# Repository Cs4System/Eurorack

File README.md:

# Eurorack

- All files are published under CC BY-NC-SA 4.0 if not marked differently

- DO NOT USE COMMERCIALLY!

- Build for yourself or for a friend, but do not sell builds, PCBs, pannels or any parts of the designes in this repository! 

- Feel free to modify, copy and use all files provided here. 
If you want to publish derivative work, please do so under same license as original

- Any feedback and collaboration is very welcome!

- Please feel free to [open an issue on the issues tab](https://github.com/Cs4System/Eurorack/issues)

**Have you built a module and would like to say thank you?** https://paypal.me/LorenzNeumann

## [Blattwerk - Betula](https://github.com/Cs4System/Eurorack/tree/main/Betula)

- 8 channels In/Out ADAT Interface
- Outputs are DC coupled
- Inputs can be switched with jumpers between AC and DC coupling (In 2 groups: channel 1-4 and channel 5-8)
- Low noise: -110dB
- Low THD: >0.01% @ 1kHz, -6dB(+-5Vpp)
- 22kOhm input-impedance, 1kOhm output-impedance
- 8HP
- All channels with bicolored indicator LED
- ADAT sync indicator LED
- No μController, no programming required, hardware only
- CC BY-NC-SA 4.0 DO NOT USE COMMERCIALY!
- small and dense SMD build (0603,TSSOP)
- 180mA @ +12V and 100mA @ -12V
(Without connected ADTA-signal:
14mA @ +12V and 0mA @ -12V)

## [Blattwerk - Salix](https://github.com/Cs4System/Eurorack/tree/main/Salix)

- VCF based on the Moog Transistor Ladder Filter
- Compensation for loss of bass in high resonance settings via potentiometer
- 6,12,18,24 dB/Oct selectable via potentiometer or CV!
- 2 Inputs with attenuator for audio and CV
- Seperate V/Oct input.
- Input-Drive indicator LED
- 8HP
- small and dense SMD build (0603, SOIC, SOT-363!) Not a beginner build, please be sure to have some SMD-soldering practice!
- 45mA @ +12V and 25mA @ -12V
- quick demo: https://youtu.be/XMdGtwIK5IQ

## [Transistor Ladder VCF](https://github.com/Cs4System/Eurorack/tree/main/Transistor_Ladder_VCF)

- Deprecated version of [Salix VCF](https://github.com/Cs4System/Eurorack/tree/main/Salix)
- VCF based on the Moog Transistor Ladder Filter
- Compensation for loss of bass in high resonance settings via potentiometer
- 6,12,18,24 dB/Oct selectable via potentiometer or CV!
- 2 Inputs with attenuator for audio and CV
- Seperate V/Oct input.
- Input-Drive indicator LED
- 8HP
- CC BY-NC-SA 4.0
- small and dense SMD build (0603, SOIC, SOT-363!)
- 45mA @ +12V and 25mA @ -12V
- PCB and Panel  is available at [synthCube](https://synthcube.com/cart/lorenz-neumann-diy-transistor-ladder-filter)
- Quick demo: https://youtu.be/XMdGtwIK5IQ

## [Dual Ears](https://github.com/Cs4System/Eurorack/tree/main/Dual%20Ears)
- BETA!
- Modification of Mutable Instruments Ears
- 2 seperat channels of original design, no internal contact microphone
- no jumpers, fixed values for fast Envelope Follower and Gate-Threshold of 1V 
- 4HP
- CC-BY-SA 3.0, Orginal schematics by Emilie Gillet
- small and dense SMD build (0603, TSSOP)

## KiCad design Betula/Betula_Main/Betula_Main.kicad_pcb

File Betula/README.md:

# Blattwerk - Betula

- 8 channels In/Out ADAT Interface
- Outputs are DC coupled
- Inputs can be switched with jumpers between AC and DC coupling (In 2 groups: channel 1-4 and channel 5-8)
- Low noise: -110dB
- Low THD: >0.01% @ 1kHz, -6dB(+-5Vpp)
- 22kOhm input-impedance, 1kOhm output-impedance
- 8HP
- All channels with bicolored indicator LED
- ADAT sync indicator LED
- No μController, no programming required, hardware only
- CC BY-NC-SA 4.0 DO NOT USE COMMERCIALY!
- small and dense SMD build (0603,TSSOP)
- 180mA @ +12V and 100mA @ -12V
(Without connected ADTA-signal:
14mA @ +12V and 0mA @ -12V)

For comments and feedback, please visit [Modwiggler](https://www.modwiggler.com/forum/viewtopic.php?t=283803&sid=8c5b24ebdf0f756f3375e19afba1d032)

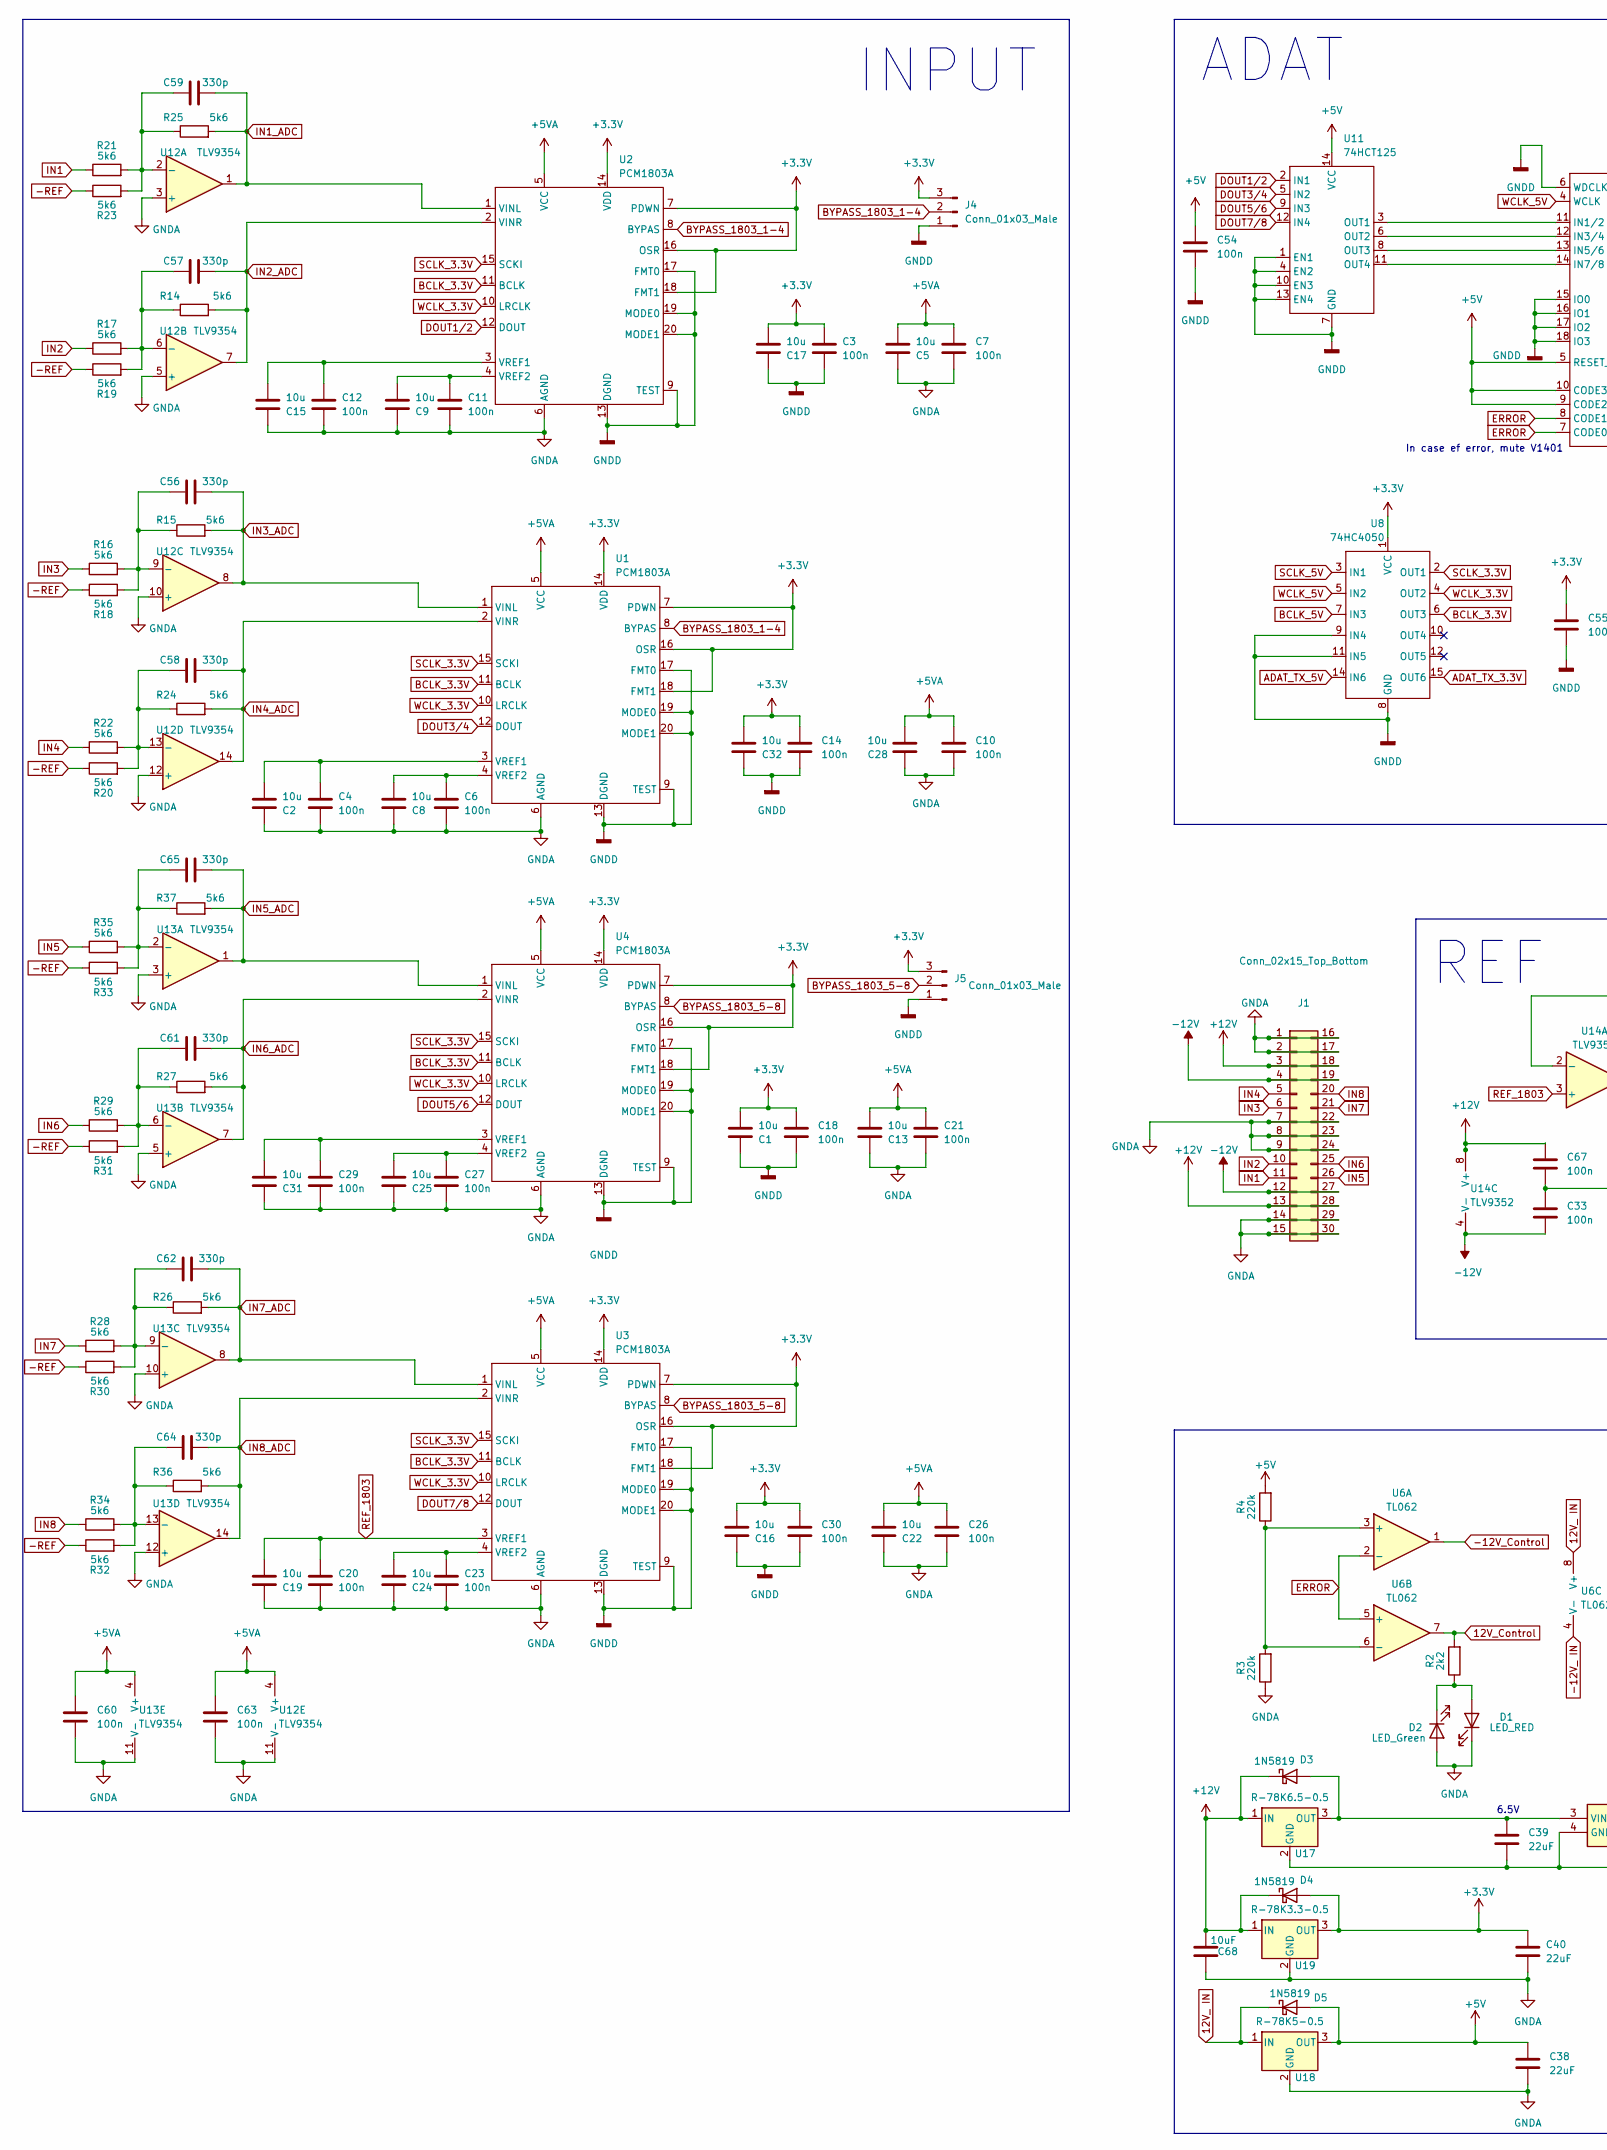
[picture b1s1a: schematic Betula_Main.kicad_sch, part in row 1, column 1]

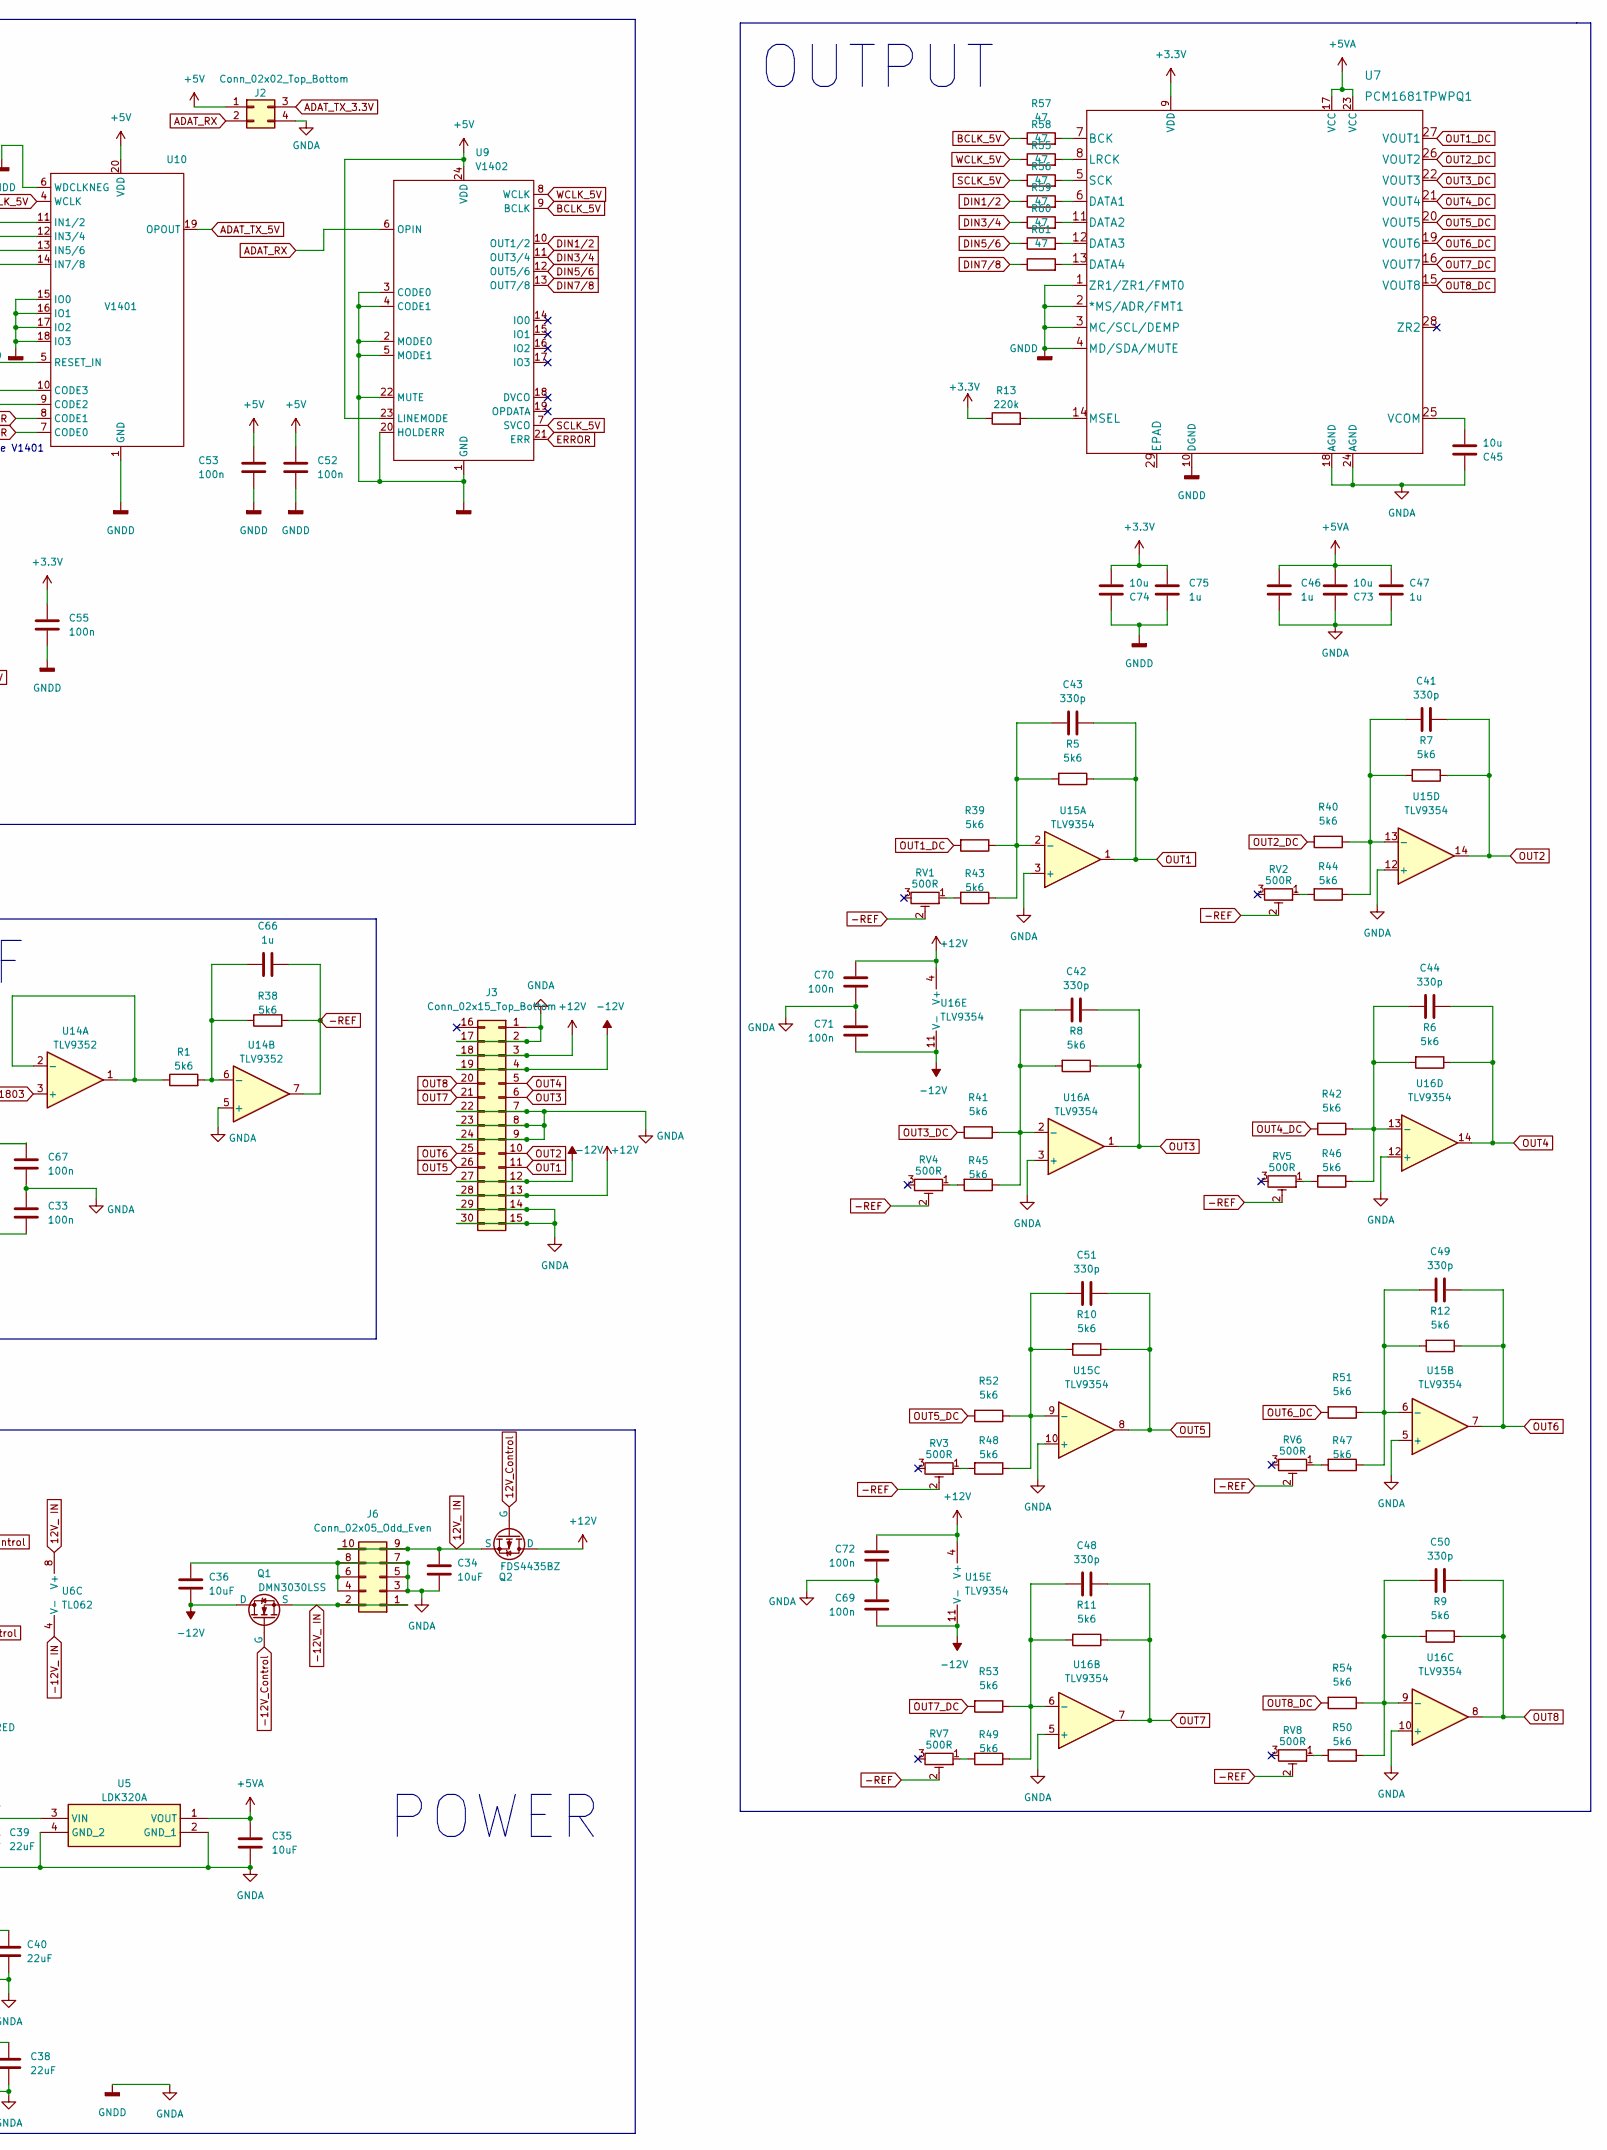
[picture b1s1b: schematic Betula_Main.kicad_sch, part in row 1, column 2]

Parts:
C1, C2, C5, C8, C9, C13, C15, C16, C17, C19, C22, C24, C25, C28, C31, C32, C45, C73, C74: 10u; C_0805_2012Metric_Pad1.18x1.45mm_HandSolder
C3, C4, C6, C7, C10, C11, C12, C14, C18, C20, C21, C23, C26, C27, C29, C30, C33, C52, C53, C54, C55, C60, C63, C67, C69, C70, C71, C72: 100n; C_0603_1608Metric_Pad1.08x0.95mm_HandSolder
C34, C35, C36, C68: 10uF; C_0805_2012Metric_Pad1.18x1.45mm_HandSolder
C38, C39, C40: 22uF; C_0805_2012Metric_Pad1.18x1.45mm_HandSolder
C41, C42, C43, C44, C48, C49, C50, C51, C56, C57, C58, C59, C61, C62, C64, C65: 330p; C_0603_1608Metric_Pad1.08x0.95mm_HandSolder
C46, C47, C66, C75: 1u; C_0603_1608Metric_Pad1.08x0.95mm_HandSolder
D1: LED_RED; LED_D3.0mm
D2: LED_Green; LED_D3.0mm
D3, D4, D5: 1N5819; D_SOD-123
J1: Conn_02x15_Top_Bottom; analogIN-Main
J2: Conn_02x02_Top_Bottom; PinHeader_2x02_P2.54mm_Vertical
J3: Conn_02x15_Top_Bottom; Output-Main
J4, J5: Conn_01x03_Male; PinHeader_1x03_P2.54mm_Vertical
J6: Conn_02x05_Odd_Even; Multicomp_MC9A12-1034_2x05x2.54mm_Straight
Q1: DMN3030LSS; SO-8_3.9x4.9mm_P1.27mm
Q2: FDS4435BZ; SO-8_3.9x4.9mm_P1.27mm
R1, R5, R6, R7, R8, R9, R10, R11, R12, R14, R15, R16, R17, R18, R19, R20, R21, R22, R23, R24, R25, R26, R27, R28, R29, R30, R31, R32, R33, R34, R35, R36, R37, R38, R39, R40, R41, R42, R43, R44, R45, R46, R47, R48, R49, R50, R51, R52, R53, R54: 5k6; R_0603_1608Metric_Pad0.98x0.95mm_HandSolder
R2: 2k2; R_0603_1608Metric_Pad0.98x0.95mm_HandSolder
R3, R4, R13: 220k; R_0603_1608Metric_Pad0.98x0.95mm_HandSolder
R55, R56, R57, R58, R59, R60, R61: 47; R_0603_1608Metric_Pad0.98x0.95mm_HandSolder
RV1, RV2, RV3, RV4, RV5, RV6, RV7, RV8: 500R; Potentiometer_Bourns_TC33X_Vertical
U1, U2, U3, U4: PCM1803A; SSOP-20_5.3x7.2mm_P0.65mm
U5: LDK320A; SOT-89-3; Manufacturer_Part_Number LDK320ADU50R; Mouser Part Number 511-LDK320ADU50R
U6: TL062; SOIC-8_3.9x4.9mm_P1.27mm
U7: PCM1681TPWPQ1
U8: 74HC4050; SO-16_3.9x9.9mm_P1.27mm
U9: V1402; SOP-24_7.5x15.4mm_P1.27mm
U10: V1401; SOP-20_7.5x12.8mm_P1.27mm
U11: 74HCT125; SO-14_3.9x8.65mm_P1.27mm
U12, U13, U15, U16: TLV9354; SOIC-14_3.9x8.7mm_P1.27mm
U14: TLV9352; SOIC-8_3.9x4.9mm_P1.27mm
U17: R-78K6.5-0.5; Converter_DCDC_RECOM_R-78K
U18: R-78K5-0.5; Converter_DCDC_RECOM_R-78K
U19: R-78K3.3-0.5; Converter_DCDC_RECOM_R-78K

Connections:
12V_ IN: C34.2, D5.1 (K), J6.9, J6.10, Q2.1 (S), Q2.2 (S), Q2.3 (S), U6.8 (V+), U18.1 (IN)
12V_Control: Q2.4 (G), R2.2, U6.7
+3.3V: C1.1, C3.2, C14.2, C16.1, C17.1, C18.2, C30.2, C32.1, C40.2, C55.2, C74.1, C75.2, D4.2 (A), J4.3, J5.3, R13.1, U1.7 (PDWN), U1.14 (VDD), U1.16 (OSR), U1.18 (FMT1), U2.7 (PDWN), U2.14 (VDD), U2.16 (OSR), U2.18 (FMT1), U3.7 (PDWN), U3.14 (VDD), U3.16 (OSR), U3.18 (FMT1), U4.7 (PDWN), U4.14 (VDD), U4.16 (OSR), U4.18 (FMT1), U7.9 (VDD), U8.1 (VCC), U19.3 (OUT)
+5V: C38.2, C52.2, C53.2, C54.2, D5.2 (A), J2.1, R4.2, U9.23 (LINEMODE), U9.24 (VDD), U10.5 (RESET_IN), U10.9 (CODE2), U10.10 (CODE3), U10.20 (VDD), U11.14 (VCC), U18.3 (OUT)
+5VA: C5.1, C7.2, C10.2, C13.1, C21.2, C22.1, C26.2, C28.1, C35.2, C46.2, C47.2, C60.2, C63.2, C73.1, U1.5 (VCC), U2.5 (VCC), U3.5 (VCC), U4.5 (VCC), U5.1 (VOUT), U7.17 (VCC), U7.23 (VCC), U12.4 (V+), U13.4 (V+)
+12V: C67.2, C68.2, C70.2, C72.2, D3.1 (K), D4.1 (K), J1.3, J1.13, J1.18, J1.28, J3.3, J3.13, J3.18, J3.28, Q2.5 (D), Q2.6 (D), Q2.7 (D), Q2.8 (D), U14.8 (V+), U15.4 (V+), U16.4 (V+), U17.1 (IN), U19.1 (IN)
-12V: C33.1, C36.1, C69.1, C71.1, J1.4, J1.12, J1.19, J1.27, J3.4, J3.12, J3.19, J3.27, Q1.5 (D), Q1.6 (D), Q1.7 (D), Q1.8 (D), U14.4 (V-), U15.11 (V-), U16.11 (V-)
-12V_ IN: J6.1, J6.2, Q1.1 (S), Q1.2 (S), Q1.3 (S), U6.4 (V-)
-12V_Control: Q1.4 (G), U6.1
-REF: C66.1, R18.1, R19.1, R20.1, R23.1, R30.1, R31.1, R32.1, R33.1, R38.2, RV1.2, RV2.2, RV3.2, RV4.2, RV5.2, RV6.2, RV7.2, RV8.2, U14.7
ADAT_RX: J2.2, U9.6 (OPIN)
ADAT_TX_3.3V: J2.3, U8.15 (OUT6)
ADAT_TX_5V: U8.14 (IN6), U10.19 (OPOUT)
BCLK_3.3V: U1.11 (BCLK), U2.11 (BCLK), U3.11 (BCLK), U4.11 (BCLK), U8.6 (OUT3)
BCLK_5V: R57.1, U8.7 (IN3), U9.9 (BCLK)
BYPASS_1803_1-4: J4.2, U1.8 (BYPAS), U2.8 (BYPAS)
BYPASS_1803_5-8: J5.2, U3.8 (BYPAS), U4.8 (BYPAS)
DIN1/2: R56.1, U9.10 (OUT1/2)
DIN3/4: R59.1, U9.11 (OUT3/4)
DIN5/6: R60.1, U9.12 (OUT5/6)
DIN7/8: R61.1, U9.13 (OUT7/8)
DOUT1/2: U2.12 (DOUT), U11.2 (IN1)
DOUT3/4: U1.12 (DOUT), U11.5 (IN2)
DOUT5/6: U4.12 (DOUT), U11.9 (IN3)
DOUT7/8: U3.12 (DOUT), U11.12 (IN4)
ERROR: U6.2 (-), U6.5 (+), U9.21 (ERR), U10.7 (CODE0), U10.8 (CODE1)
GNDA: C1.2, C2.2, C3.1, C4.2, C5.2, C6.2, C7.1, C8.2, C9.2, C10.1, C11.2, C12.2, C13.2, C14.1, C15.2, C16.2, C17.2, C18.1, C19.2, C20.2, C21.1, C22.2, C23.2, C24.2, C25.2, C26.1, C27.2, C28.2, C29.2, C30.1, C31.2, C32.2, C33.2, C34.1, C35.1, C36.2, C38.1, C39.1, C40.1, C45.2, C46.1, C47.1, C52.1, C53.1, C54.1, C55.1, C60.1, C63.1, C67.1, C68.1, C69.2, C70.1, C71.2, C72.1, C73.2, C74.2, C75.1, D1.1 (K), D2.2 (A), J1.1, J1.2, J1.7, J1.8, J1.9, J1.14, J1.15, J1.16, J1.17, J1.22, J1.23, J1.24, J1.29, J1.30, J2.4, J3.1, J3.2, J3.7, J3.8, J3.9, J3.14, J3.15, J3.17, J3.22, J3.23, J3.24, J3.29, J3.30, J4.1, J5.1, J6.3, J6.4, J6.5, J6.6, J6.7, J6.8, R3.1, U1.6 (AGND), U1.9 (TEST), U1.13 (DGND), U1.17 (FMT0), U1.19 (MODE0), U1.20 (MODE1), U2.6 (AGND), U2.9 (TEST), U2.13 (DGND), U2.17 (FMT0), U2.19 (MODE0), U2.20 (MODE1), U3.6 (AGND), U3.9 (TEST), U3.13 (DGND), U3.17 (FMT0), U3.19 (MODE0), U3.20 (MODE1), U4.6 (AGND), U4.9 (TEST), U4.13 (DGND), U4.17 (FMT0), U4.19 (MODE0), U4.20 (MODE1), U5.2 (GND_1), U5.4 (GND_2), U7.1 (ZR1/ZR1/FMT0), U7.2 (*MS/ADR/FMT1), U7.3 (MC/SCL/DEMP), U7.4 (MD/SDA/MUTE), U7.10 (DGND), U7.18 (AGND), U7.24 (AGND), U8.8 (GND), U8.9 (IN4), U8.11 (IN5), U9.1 (GND), U9.2 (MODE0), U9.3 (CODE0), U9.4 (CODE1), U9.5 (MODE1), U9.20 (HOLDERR), U9.22 (MUTE), U10.1 (GND), U10.6 (WDCLKNEG), U10.15 (IO0), U10.16 (IO1), U10.17 (IO2), U10.18 (IO3), U11.1 (EN1), U11.4 (EN2), U11.7 (GND), U11.10 (EN3), U11.13 (EN4), U12.3 (+), U12.5 (+), U12.10 (+), U12.11 (V-), U12.12 (+), U13.3 (+), U13.5 (+), U13.10 (+), U13.11 (V-), U13.12 (+), U14.5 (+), U15.3 (+), U15.5 (+), U15.10 (+), U15.12 (+), U16.3 (+), U16.5 (+), U16.10 (+), U16.12 (+), U17.2 (GND), U18.2 (GND), U19.2 (GND)
IN1: J1.11, R21.1
IN1_ADC: C59.2, R25.2, U2.1 (VINL), U12.1
IN2: J1.10, R17.1
IN2_ADC: C57.2, R14.2, U2.2 (VINR), U12.7
IN3: J1.6, R16.1
IN3_ADC: C56.2, R15.2, U1.1 (VINL), U12.8
IN4: J1.5, R22.1
IN4_ADC: C58.2, R24.2, U1.2 (VINR), U12.14
IN5: J1.26, R35.1
IN5_ADC: C65.2, R37.2, U4.1 (VINL), U13.1
IN6: J1.25, R29.1
IN6_ADC: C61.2, R27.2, U4.2 (VINR), U13.7
IN7: J1.21, R28.1
IN7_ADC: C62.2, R26.2, U3.1 (VINL), U13.8
IN8: J1.20, R34.1
IN8_ADC: C64.2, R36.2, U3.2 (VINR), U13.14
unnamed: D1.2 (A), D2.1 (K), R2.1
unnamed: C39.2, D3.2 (A), U5.3 (VIN), U17.3 (OUT)
unnamed: R43.2, RV1.1
unnamed: R44.2, RV2.1
unnamed: R45.2, RV4.1
unnamed: R46.2, RV5.1
unnamed: R47.2, RV6.1
unnamed: R48.2, RV3.1
unnamed: R49.2, RV7.1
unnamed: R50.2, RV8.1
unnamed: C2.1, C4.1, U1.3 (VREF1)
unnamed: C6.1, C8.1, U1.4 (VREF2)
unnamed: C12.1, C15.1, U2.3 (VREF1)
unnamed: C9.1, C11.1, U2.4 (VREF2)
unnamed: C23.1, C24.1, U3.4 (VREF2)
unnamed: C29.1, C31.1, U4.3 (VREF1)
unnamed: C25.1, C27.1, U4.4 (VREF2)
unnamed: R3.2, R4.1, U6.3 (+), U6.6 (-)
unnamed: R57.2, U7.7 (BCK)
unnamed: R56.2, U7.6 (DATA1)
unnamed: R59.2, U7.11 (DATA2)
unnamed: R60.2, U7.12 (DATA3)
unnamed: R61.2, U7.13 (DATA4)
unnamed: R58.2, U7.8 (LRCK)
unnamed: R13.2, U7.14 (MSEL)
unnamed: R55.2, U7.5 (SCK)
unnamed: C45.1, U7.25 (VCOM)
unnamed: U10.11 (IN1/2), U11.3 (OUT1)
unnamed: U10.12 (IN3/4), U11.6 (OUT2)
unnamed: U10.13 (IN5/6), U11.8 (OUT3)
unnamed: U10.14 (IN7/8), U11.11 (OUT4)
unnamed: C59.1, R21.2, R23.2, R25.1, U12.2 (-)
unnamed: C57.1, R14.1, R17.2, R19.2, U12.6 (-)
unnamed: C56.1, R15.1, R16.2, R18.2, U12.9 (-)
unnamed: C58.1, R20.2, R22.2, R24.1, U12.13 (-)
unnamed: C65.1, R33.2, R35.2, R37.1, U13.2 (-)
unnamed: C61.1, R27.1, R29.2, R31.2, U13.6 (-)
unnamed: C62.1, R26.1, R28.2, R30.2, U13.9 (-)
unnamed: C64.1, R32.2, R34.2, R36.1, U13.13 (-)
unnamed: R1.1, U14.1, U14.2 (-)
unnamed: C66.2, R1.2, R38.1, U14.6 (-)
unnamed: C43.2, R5.2, R39.1, R43.1, U15.2 (-)
unnamed: C49.2, R12.2, R47.1, R51.1, U15.6 (-)
unnamed: C51.2, R10.2, R48.1, R52.1, U15.9 (-)
unnamed: C41.2, R7.2, R40.1, R44.1, U15.13 (-)
unnamed: C42.2, R8.2, R41.1, R45.1, U16.2 (-)
unnamed: C48.2, R11.2, R49.1, R53.1, U16.6 (-)
unnamed: C50.2, R9.2, R50.1, R54.1, U16.9 (-)
unnamed: C44.2, R6.2, R42.1, R46.1, U16.13 (-)
OUT1: C43.1, J3.11, R5.1, U15.1
OUT1_DC: R39.2, U7.27 (VOUT1)
OUT2: C41.1, J3.10, R7.1, U15.14
OUT2_DC: R40.2, U7.26 (VOUT2)
OUT3: C42.1, J3.6, R8.1, U16.1
OUT3_DC: R41.2, U7.22 (VOUT3)
OUT4: C44.1, J3.5, R6.1, U16.14
OUT4_DC: R42.2, U7.21 (VOUT4)
OUT5: C51.1, J3.26, R10.1, U15.8
OUT5_DC: R52.2, U7.20 (VOUT5)
OUT6: C49.1, J3.25, R12.1, U15.7
OUT6_DC: R51.2, U7.19 (VOUT6)
OUT7: C48.1, J3.21, R11.1, U16.7
OUT7_DC: R53.2, U7.16 (VOUT7)
OUT8: C50.1, J3.20, R9.1, U16.8
OUT8_DC: R54.2, U7.15 (VOUT8)
REF_1803: C19.1, C20.1, U3.3 (VREF1), U14.3 (+)
SCLK_3.3V: U1.15 (SCKI), U2.15 (SCKI), U3.15 (SCKI), U4.15 (SCKI), U8.2 (OUT1)
SCLK_5V: R55.1, U8.3 (IN1), U9.7 (SVCO)
WCLK_3.3V: U1.10 (LRCLK), U2.10 (LRCLK), U3.10 (LRCLK), U4.10 (LRCLK), U8.4 (OUT2)
WCLK_5V: R58.1, U8.5 (IN2), U9.8 (WCLK), U10.4 (WCLK)

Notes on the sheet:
POWER
REF
ADAT
INPUT
6.5V
In case ef error, mute V1401
OUTPUT

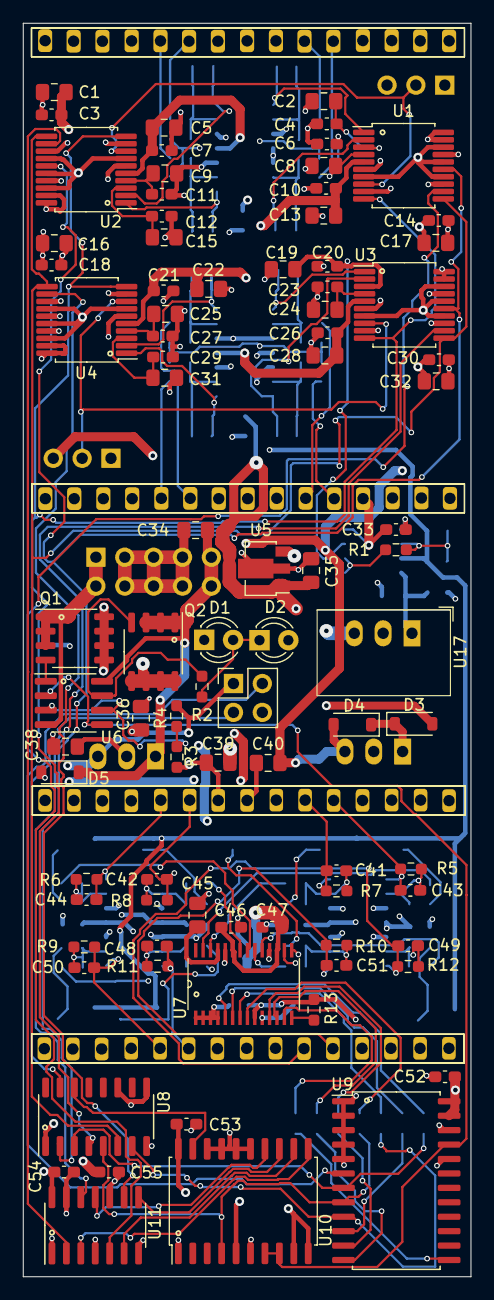
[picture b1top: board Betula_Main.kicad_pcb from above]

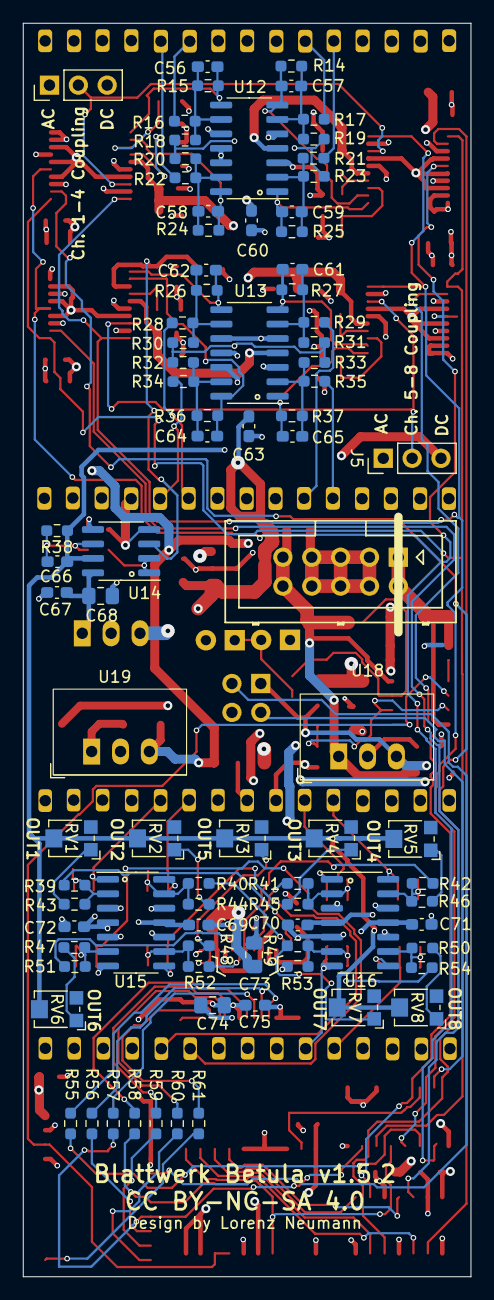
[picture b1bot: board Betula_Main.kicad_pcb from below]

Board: 4 copper layers, 39.4 x 110.3 mm, 175 parts (86 on the bottom side), 113 nets.

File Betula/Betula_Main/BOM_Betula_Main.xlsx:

Reference(s) | Qty | Value | Footprint | Mouser | Comment
R3,R4,R13 | 3 | 220k | R_0603 | 603-RC0603FR-07220KL
R1,R5,R6,R7,R8,R9,R10,R11,R12,R14,R15,R16,R17,R18,R19,R20,R21,R22,R23,R24,R25,R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 | 50 | 5k6 | R_0603 | 603-RC0603FR-075K6L
R2 | 1 | 2k2 | R_0603 | 603-RC0603FR-072K2L
R55,R56,R57,R58,R59,R60,R61 | 7 | 47R | R_0603 | 603-RC0603FR-0747RL
RV1,RV2,RV3,RV4,RV5,RV6,RV7,RV8 | 8 | 500R | TC33X | 652-TC33X-2-501E
C3,C4,C6,C7,C10,C11,C12,C14,C18,C20,C21,C23,C26,C27,C29,C30,C33,C52,C53,C54,C55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 | 28 | 100n | C_0603 | 80-C0603C104J5RACLR
C38,C39,C40 | 3 | 22u | C_0805 | 187-CL21A226MOCLRNC
C1,C2,C5,C8,C9,C13,C15,C16,C17,C19,C22,C24,C25,C28,C31,C32,C34,C35,C36,C45,C68,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 | 23 | 10u | C_0805 | 81-GRM21BR61H106KE3L
C46,C47,C66,C75 | 4 | 1u | C_0603 | 603-CC603KRX5R8BB105
C41,C42,C43,C44,C48,C49,C50,C51,C56,C57,C58,C59,C61,C62,C64,C65 | 16 | 330p | C_0603 | 187-CL10C331JB8NNNC | C0G Type!
D2 | 1 | LED_Green | 3mm | 604-WP710A10CGCK
D1 | 1 | LED Red | 3mm | 696-SSLLX3044SRC/D
D3, D4,D5 | 3 | 1N5819 | SOD-123 | 621-1N5819HW-F
U6 | 1 | TL062 | SOIC-8_3.9x4.9mm_P1.27mm | 595-TL062CDR
U1,U2,U3,U4 | 4 | PCM1803A | SSOP-20_5.3x7.2mm_P0.65mm | 595-PCM1803ADBR
U11 | 1 | 74HCT125 | SO-14_3.9x8.65mm_P1.27mm | 771-74HCT125D-T
U10 | 1 | V1401 | SOP-20_7.5x12.8mm_P1.27mm |  | www.cabintechglobal.com
U8 | 1 | 74HC4050 | SO-16_3.9x9.9mm_P1.27mm | 771-74HC4050D-T
U9 | 1 | V1402 | SOP-24_7.5x15.4mm_P1.27mm |  | www.cabintechglobal.com
U5 | 1 | n | SOT89 | 511-LDK320AU50R
U12,U13,U15,U16 | 4 | TLV9354 | SOIC-14_3.9x8.7mm_P1.27mm | 595-TLV9354IDR | U15 and U16 can be TL074C, higher currend draw (+ 6mA on both rails). U12,U13 c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
U14 | 1 | OPA1692 | SOIC-8_3.9x4.9mm_P1.27mm | 595-TLV9352IDR | TL072C works as well. Higher currend draw (+ 1.5mA on both rails) and a little 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
U7 | 1 | PCM1681 | HTSSOP-28 | 595-PCM1681PWPR
Q2 | 1 | FDS4435BZ | SO-8_3.9x4.9mm_P1.27mm | 512-FDS4435BZ
Q1 | 1 | DMN3030LSS | SO-8_3.9x4.9mm_P1.27mm | 621-DMN3030LSS-13
U17 | 1 | R-78K6.5-0.5 |  | 919-R-78K6.5-0.5
U18 | 1 | R-78K5.0-0.5 |  | 919-R-78K5.0-0.5
U19 | 1 | R-78K63.3-0.5 |  | 919-R-78K3.3-0.5
 | 4 | 15x1 Pin Header Socket
 | 2 | 1x3 Pin Header Male
 | 1 | 2x2 Pin Header Socket
 | 1 | 02x05 Power connector

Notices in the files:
Betula/Betula_Input/Betula_Input.kicad_pcb:
CC BY-NC-SA 4.0 Design by Lorenz Neumann
parts and their libraries:
Copyright 2021 Accelerated Designs. All rights reserved.
